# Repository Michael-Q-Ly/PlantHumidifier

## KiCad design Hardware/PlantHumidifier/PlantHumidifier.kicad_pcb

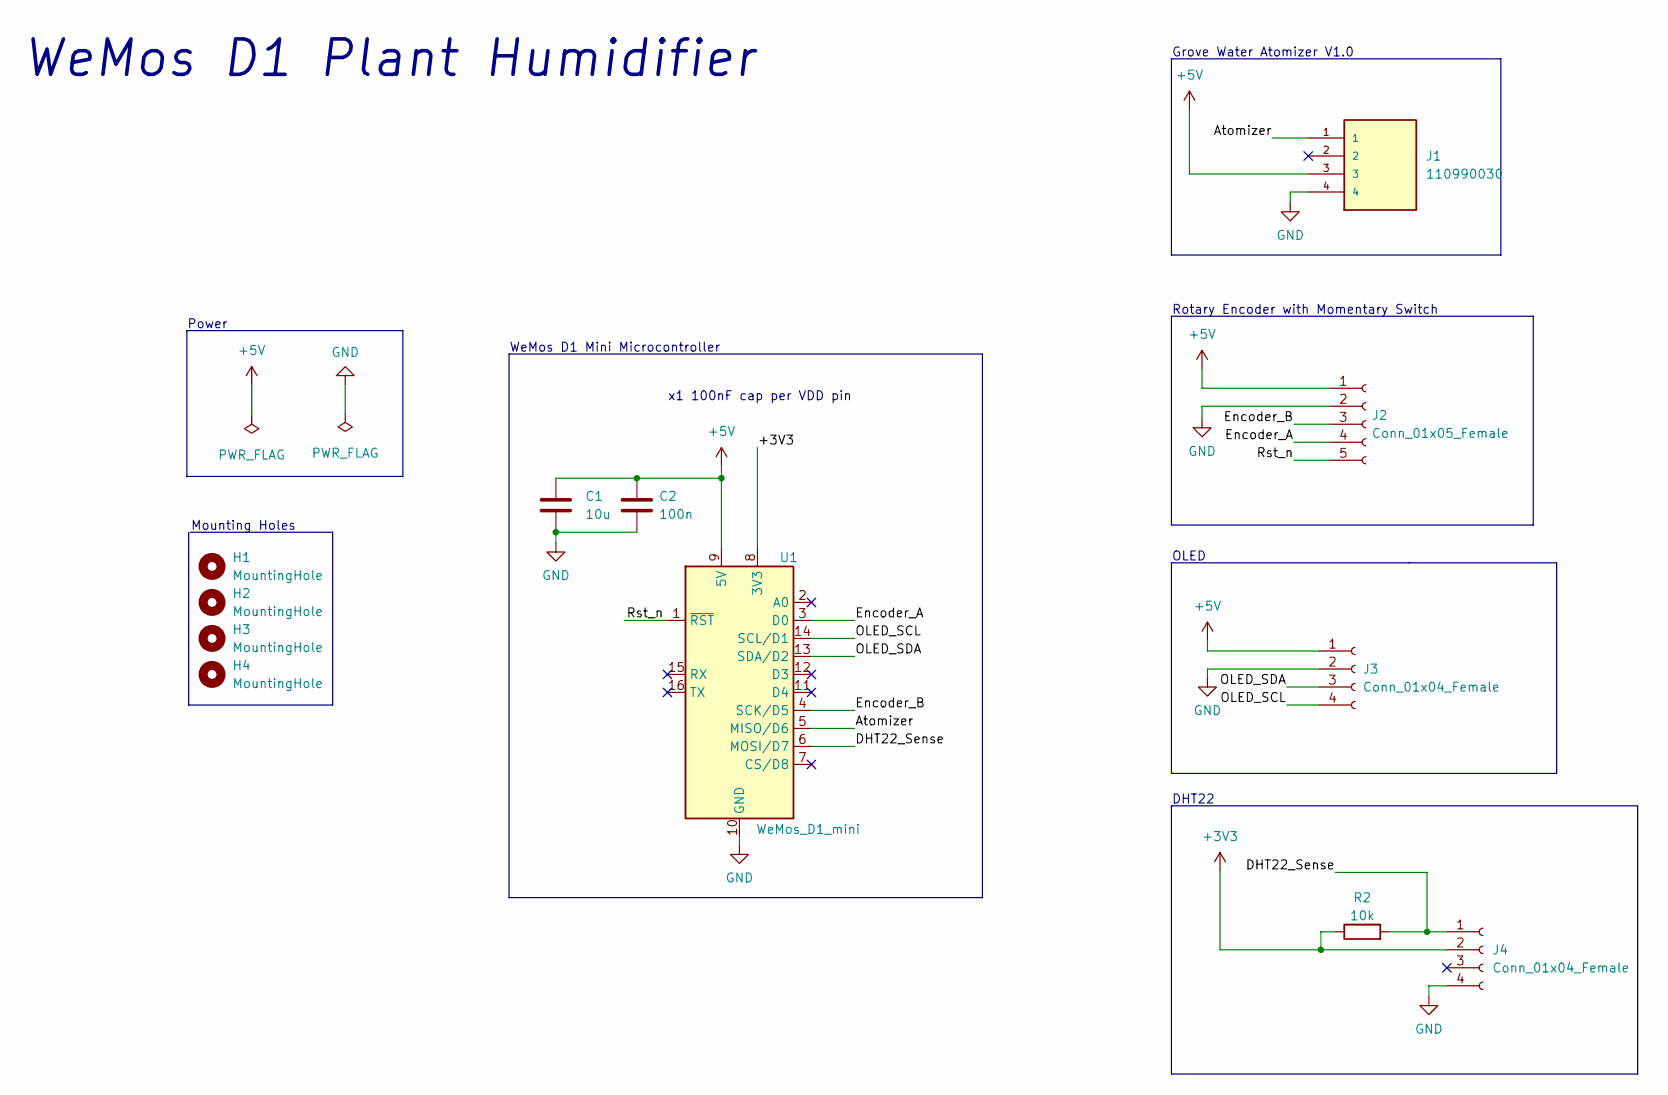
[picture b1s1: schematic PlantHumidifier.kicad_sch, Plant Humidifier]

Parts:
C1: 10u; C_0603_1608Metric
C2: 100n; C_0402_1005Metric
H1, H2, H3, H4: MountingHole; MountingHole_2.2mm_M2
J1: 110990030; SEEED_110990030; PARTREV A
J2: Conn_01x05_Female; JST_XH_B5B-XH-A_1x05_P2.50mm_Vertical
J3, J4: Conn_01x04_Female; JST_XH_B4B-XH-A_1x04_P2.50mm_Vertical
R2: 10k; R_0402_1005Metric
U1: WeMos_D1_mini; WEMOS_D1_mini_light

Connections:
+3V3: J4.2, R2.1, U1.8 (3V3)
+5V: C1.1, C2.1, J1.3, J2.1, J3.1, U1.9 (5V)
/Atomizer: J1.1, U1.5 (MISO/D6)
/DHT22_Sense: J4.1, R2.2, U1.6 (MOSI/D7)
/Encoder_A: J2.4, U1.3 (D0)
/Encoder_B: J2.3, U1.4 (SCK/D5)
/OLED_SCL: J3.4, U1.14 (SCL/D1)
/OLED_SDA: J3.3, U1.13 (SDA/D2)
/Rst_n: J2.5, U1.1 (~RST)
GND: C1.2, C2.2, J1.4, J2.2, J3.2, J4.4, U1.10 (GND)

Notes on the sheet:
x1 100nF cap per VDD pin
Rotary Encoder with Momentary Switch
OLED
DHT22
Grove Water Atomizer V1.0
WeMos D1 Mini Microcontroller
Power
Mounting Holes
WeMos D1 Plant Humidifier

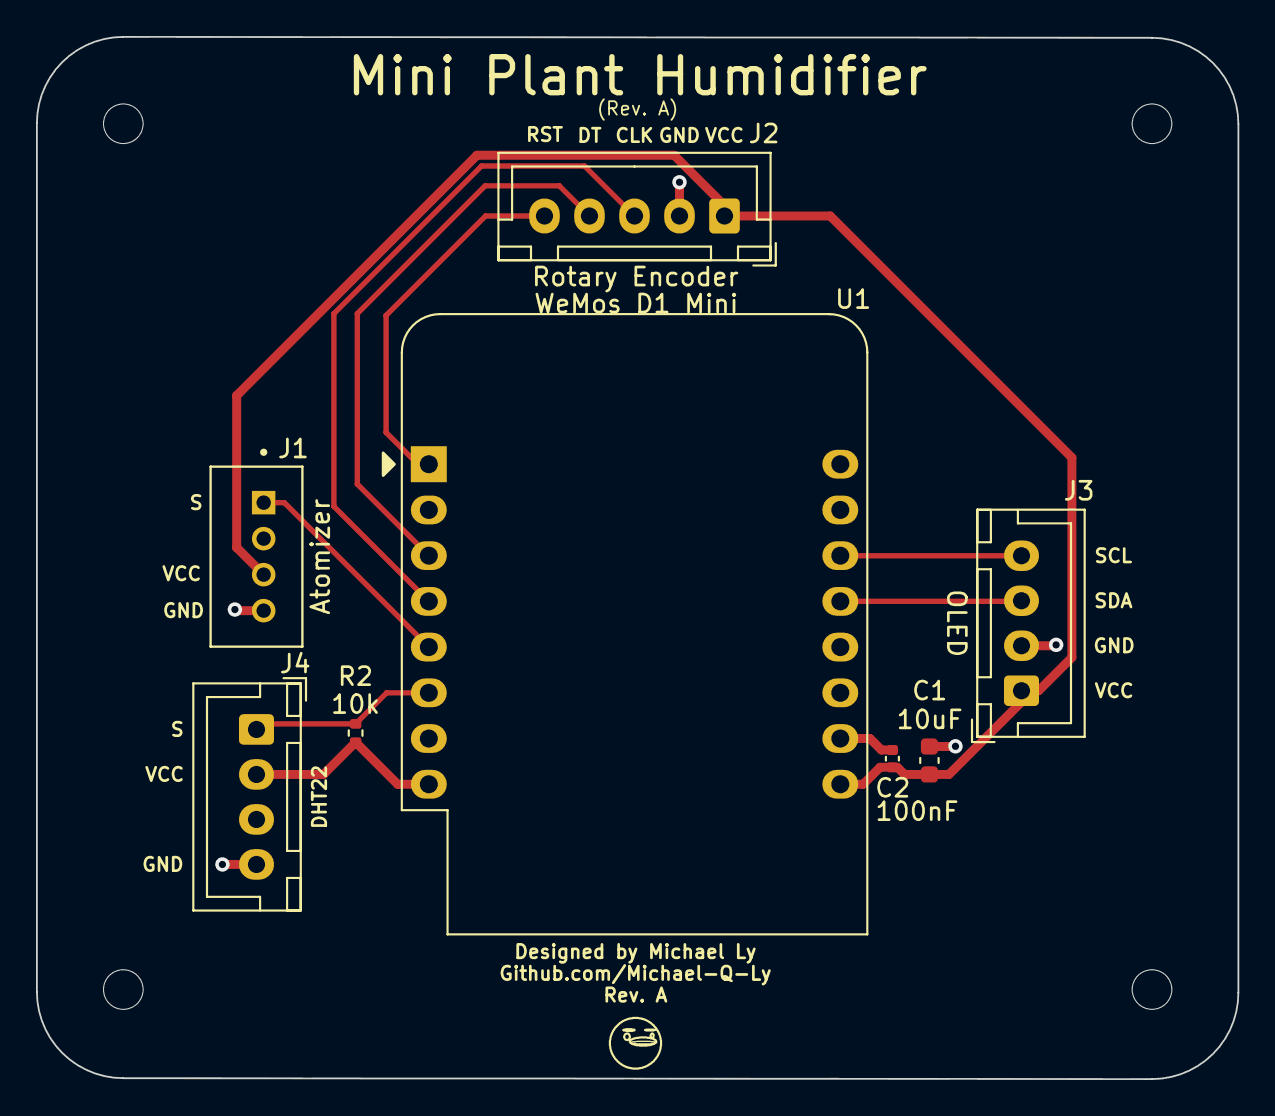
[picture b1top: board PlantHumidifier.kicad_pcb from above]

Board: 2 copper layers, 66.8 x 57.9 mm, 12 parts (0 on the bottom side), 10 nets.

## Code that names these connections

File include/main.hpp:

/*
 * =====================================================================================
 *
 *       Filename:  main.hpp
 *
 *    Description:  Main header file 
 *
 *        Version:  1.0
 *        Created:  01/07/2023 06:40:18 PM
 *       Revision:  none
 *       Compiler:  g++
 *
 *         Author:  Michael Ly
 *   Organization:  
 *
 * =====================================================================================
 */
#ifndef MAIN_HPP
#define MAIN_HPP

#include <Arduino.h>

#define BAUD_RATE			115200

#define uS_TO_S				1000

#define TIME_BETWEEN_MEASURE		(1 * uS_TO_S)
#define TIME_BETWEEN_FAILED_MEASURE	(2 * uS_TO_S)
#define DISPLAY_WELCOME_TIME		(5 * uS_TO_S)


/*-----------------------------------------------------------------------------
 * PINS 
 *-----------------------------------------------------------------------------*/

#define ATOMIZER_PIN		12
#define DHT_PIN			13
#define ENCODER_A_PIN		16
#define ENCODER_B_PIN		14

#endif /* MAIN_HPP */

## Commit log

2022-12-31 Create new PlatformIO project
2022-12-31 Add example code from Adafruit for DHT sensors
2022-12-31 Add Adafruit_SSD1306 library (includes Adafruit_GFX)
2023-01-01 Confirm that the OLED screen works with Hello World Message
    - Ensure that the OLED screen VCC line is biased with a minimum
    of ~3.6VDC to 5VDCC. You can use the 5V output of the D1_Mini
    to power it; the 3V line will NOT work
2023-01-02 Show hudmidity, temperature, and heat index on OLED successfully
2023-01-02 Add KiCad to gitignore
2023-01-02 Schematic: start water atomizer schematic
2023-01-03 Copy current project to an example that uses OLED to display DHT data
2023-01-06 Add water atomizer module
2023-01-06 Add ESP8266TimerInterrupt library to project and begin refactor
2023-01-06 Refactor code to use Functions and begin work on encoder
    - The following are now functions:
    - Displaying welcoem screen on OLED
    - Displaying data through OLED
    - Verifying if DHTxx read data correctly
2023-01-08 Add encoder proof of concept
2023-01-08 Finish refactoring functions into separate modules; begin encoder modules
2023-01-08 Get water atomizer to use nonblocking code to turn on
    - Not using some sort of delayed time to turn on and off will
    cause the water atomizer to PWM its on/off time, which will
    not let it pull up to logical value 1 due to average voltage
    level
    - The fix applied here will get millis to use as nonblocking
    code, thus allowing atomizer to turn on for a duration before
2023-01-09 Add enumeration for atomizer on and off positions
2023-01-09 Begin plant humidifier PCB
2023-01-10 Schematic: Add D1 mini
2023-01-12 Schematic: Layout connectors for all sensors
2023-01-12 Schematic: Add filtering caps and wire DHT22
2023-01-12 Schematic: Wire up OLED screen
2023-01-12 Schematic: Finish wiring rotary encoder with momentary switch
2023-01-12 Schematic: Finish wiring Grove water atomizer
2023-01-12 Schematic: Fix pin connections of sensors
2023-01-12 Move DHT22 pin in code and schematic to D3 (GPIO 0); GPIO requires removal of DHT b/w resets
2023-01-12 Exclude autosave files from PCB design in gitignore
2023-01-12 Schematic: Add an active low reset switch
2023-01-12 Schematic: Add page Title + Info
2023-01-12 Schematic: Finish adding title and drawing outlines for different modules
2023-01-12 Schematic: Annotate schematic
2023-01-12 Schematic: Run and fix DRC + Add power
2023-01-13 Schematic: Fix switch to momentary switch
2023-01-13 Schematic: Add footprints (except for water atomizer)
2023-01-13 Schematic: Add symbol/Footprints for atomizer and finish footprint assignment
2023-01-13 Layout: Begin Plant Humidifier layout
2023-01-13 Schematic: Fix unlabeled part and run ERC again
2023-01-13 Layout: Update PCB from schematic
2023-01-13 Layout: Add board settings for OSH Park
2023-01-13 Layout: Route DHT22
2023-01-13 Layout: Route OLED screen
2023-01-14 Code: Remove encoder switch pin to use as HW reset only and move atomizer and DHT pins around for layout
2023-01-14 Schematic: Reflect changes in pin assignment
2023-01-14 Layout: Reflect new pin changes
2023-01-14 Change pin assignment for OLED for better routing
2023-01-14 Layout: Route OLED
2023-01-14 Update pins again for easier routing (reflected in layout + schematic here as well)
2023-01-14 Layout: Route encoder and atomizer
2023-01-14 Layout: Route power and ground rails
2023-01-14 Schematic: Add mounting holes (Size M2)
2023-01-14 Layout: Make edge cuts
2023-01-14 Layout: Add copper pour
2023-01-14 Layout: Fix all DRC errors
2023-01-14 Layout: Center Encoder
2023-01-14 Layout: Add silkscreen values, headers, & values
2023-01-14 Schematic: Update annotations
2023-01-14 Add custom Ducky image and footprint
2023-01-14 Layout: Add silkscreen title and relevant information about design
2023-01-14 Layout: Generate manufacturing files such as BOM, position, gbr, and drill files
2023-01-14 Code: Change welcome screen
2023-01-14 give new title to README to reflect project status
